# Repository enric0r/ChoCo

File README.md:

# ChoCo

**A USB MIDI chord controller built around a Raspberry Pi Pico.**

Choose a scale, hold a degree key, and move the joystick to change the chord. ChoCo sends MIDI notes to a software instrument, DAW, or compatible MIDI host; the connected instrument produces the sound. The OLED shows the current chord and playing modes.

[Website](https://enric0r.github.io/choco.github.io/) · [English handbook](https://enric0r.github.io/choco.github.io/docs/) · [Guida in italiano](https://enric0r.github.io/choco.github.io/it/docs/) · [Releases](https://github.com/enric0r/ChoCo/releases)

## What you can play

- **Chords in a scale.** Seven degree keys select diatonic chords. Change the root note and choose from nine scales.
- **Chord variations.** Move the joystick for suspensions, sevenths, extensions and other variations. Return it to the center for the base triad.
- **Different ways to play.** Use latch to sustain a chord, add a bass note, stagger notes with strum, or switch to single notes.
- **Inversions and voicing.** Store an inversion for each degree or enable smart voicing.
- **Feedback on the device.** The 128×64 OLED shows key, scale, chord, mode badges and harmonic suggestions.

ChoCo sends class-compliant USB MIDI through TinyUSB. This repository contains the firmware, KiCad hardware files and [STL files for the case](hardware/case/).

## Play your first chord

For an assembled controller:

1. Install the firmware if needed. Download a UF2 from [Releases](https://github.com/enric0r/ChoCo/releases), when available, or [build it below](#build-and-flash).
2. Connect ChoCo with a USB **data** cable.
3. Select its USB MIDI input in your DAW or MIDI host and load an instrument.
4. Hold key `0` to play the first degree of the selected scale.
5. Move the joystick while holding the key, then return it to the center to hear the base chord again.

Start with the [English setup guide](https://enric0r.github.io/choco.github.io/docs/#get-started) or [guida italiana](https://enric0r.github.io/choco.github.io/it/docs/#get-started) for the full walkthrough.

## Controls at a glance

The two upper rows sit halfway between the four white keys. Labels below follow the firmware:

```text
  A   B   C
  1   3   5
0   2   4   6
```

| Control | Action |
| --- | --- |
| `0–6` | Play one of the seven scale degrees |
| `A` | Raise the root by one semitone |
| `B` | Select the next scale |
| `C` | Hold as a modifier for shortcuts |
| Joystick tilt, with a degree held | Change the chord variation |
| `C` + `0–6` | Cycle the inversion for that degree |
| `C` + `A` | Toggle chord latch when A is released; cancelled if the joystick button is used for strum |
| Joystick short press, without `C` | Stop the chord and cancel pending strum notes, keeping the selected modes |
| Joystick long press, without `C` | Toggle single-note mode |

The [illustrated control map](https://enric0r.github.io/choco.github.io/docs/#controls) covers bass, strum, octave changes and the other shortcuts. See [chord variations](https://enric0r.github.io/choco.github.io/docs/#shape-a-chord) for the three joystick maps and [modes and display](https://enric0r.github.io/choco.github.io/docs/#modes-and-display) for the OLED guide.

## Build and flash

Install PlatformIO, then open this repository in a terminal or in VS Code with the PlatformIO extension. The firmware uses the Arduino RP2040 core and the `pico` environment.

```powershell
pio run
```

The UF2 file is written to `.pio/build/pico/firmware.uf2`. To install it:

1. Disconnect the Pico.
2. Hold **BOOTSEL** while connecting it over USB.
3. Copy the UF2 to the **RPI-RP2** drive. The board restarts automatically.

You can also upload through PlatformIO:

```powershell
pio run -t upload
```

`platformio.ini` sets `upload_port = COM5` for local development. Override it locally if your board uses another port. Keep the TinyUSB and network-disable build flags: they are required for this USB MIDI setup.

Serial logging is disabled by default. For diagnostics, set `CHOCO_LOG_LEVEL` in [Config.h](lib/Config/Config.h), rebuild, and run `pio device monitor`. See [DEBUGGING.md](DEBUGGING.md) for the diagnostic steps.

## Hardware and configuration

The prototype uses a Raspberry Pi Pico, ten keys wired as a 3×4 matrix, an analog joystick with a push switch, and an SSD1306-compatible 128×64 I²C OLED.

| Connection | Default pins |
| --- | --- |
| Keypad rows | GP2, GP1, GP0 |
| Keypad columns | GP3, GP4, GP5, GP6 |
| Joystick X / Y | A0 / A1 |
| Joystick switch | GP13 |
| OLED SDA / SCL | GP14 / GP15, on `Wire1` |

The [hardware directory](hardware/) contains the [schematic](hardware/ChoCo.kicad_sch), [PCB layout](hardware/ChoCo.kicad_pcb), [KiCad project](hardware/ChoCo.kicad_pro) and [REV-02 archive](hardware/ChoCo_REV-02.zip).

### 3D-printed case

The [case files and printing notes](hardware/case/) include three separate STL models exported from the Fusion 360 design:

- [Top frame](hardware/case/ChoCo-top.stl)
- [Chocolate-bar bottom](hardware/case/ChoCo-bar-bottom.stl)
- [Joystick cap](hardware/case/ChoCo-thumbstick.stl)

Import the files in millimeters at 100% scale. Each file contains one part; no slicer profile is included yet.

### Prototype bill of materials

For one ChoCo, the project files describe the parts below. This is a record of
the prototype design; exact purchased models and suppliers are still being
confirmed. See the [detailed BOM and assembly notes](hardware/BOM.md).

| Qty | Part | Project detail |
| --- | --- | --- |
| 1 | ChoCo PCB | Prototype marked REV-02 |
| 1 | Raspberry Pi Pico | RP2040 module, `A1` |
| 1 | 128×64 I²C OLED | SSD1306-compatible firmware; `J1` |
| 1 | Two-axis analog joystick with push switch | PS4-style footprint; exact model to confirm |
| 10 | Mechanical key switches | MX-style 1u PCB footprints; `S1–S10` |
| 10 | Matrix diodes | Axial DO-35 footprints; `D1–D10`; symbol describes the 1N4148 family |
| 10 | Keycaps | Visible in the prototype; exact model to confirm |
| 1 | Enclosure / base assembly | Visible in the prototype; fabrication details to confirm |
| 1 | USB data cable | Match the connector on the installed Pico |

Headers, sockets and mounting hardware depend on the actual assembly; they are
listed separately in the detailed BOM so they are not mistaken for additional
schematic components.

Pin assignments, joystick orientation and thresholds, display timings, logging and mode defaults live in [lib/Config/Config.h](lib/Config/Config.h). The [hardware guide](https://enric0r.github.io/choco.github.io/docs/#hardware) and [configuration reference](https://enric0r.github.io/choco.github.io/docs/#configuration) explain these settings.

## Developing the firmware

| Path | Purpose |
| --- | --- |
| [src/main.cpp](src/main.cpp) | Setup and main loop |
| [lib/Controls](lib/Controls/) | Keypad and joystick input |
| [lib/ChordEngine](lib/ChordEngine/) | Chords, inversions, voicing and history |
| [lib/Display](lib/Display/) | OLED rendering and status |
| [lib/MIDI](lib/MIDI/) | USB MIDI transport |
| [lib/Config](lib/Config/) | Shared configuration |
| [test/logic](test/logic/) | Host-side logic tests |

Read [CONTRIBUTING.md](CONTRIBUTING.md) before changing the firmware. Keep the main loop responsive and put hardware settings in `Config.h`.

<details>
<summary>OLED and input implementation notes</summary>

### OLED layout

The header shows the selected key/scale and active degree (`D1..D7`), or `EDIT`
while C is held. The chord is centered at the largest size that fits. The arrow
tracks joystick direction with the horizontal mirror removed; the existing
vertical mapping is preserved for the mounted device.

Active modes appear as a compact text line: `VOI` (smart voicing), `BAS` (bass),
`NOTE` (single note), `STR` (strum), `LAT` (latch). The footer normally shows
`NEXT` suggestions. Temporary confirmations replace only the footer so the
chord stays readable. Long text is fitted or explicitly truncated.

Startup uses a static CHOCO wordmark. The screensaver moves the same wordmark
with the selected key/scale on a separate line; it does not blink or invert.

### Responsiveness and feedback

- Each key and the joystick button use a 10 ms stable-edge debounce, including releases. A newly pressed degree takes over from a held degree; releasing it stops playback unless latch is enabled. Previously held degrees do not retrigger automatically. Exactly simultaneous presses select the lowest degree.
- Strum note-ons are scheduled without blocking input, and pending notes are cancelled on release or chord replacement. Smart voicing preserves only notes that have actually started.
- OLED updates remain limited to 100 ms, skip unchanged frames, and wait for pending strum notes. The first key press wakes the screen and performs its action. Sounding chords keep the screen awake.
- Joystick feedback and new chord attacks share the same hysteresis state, so a variation remains selected until the stick crosses the release threshold. Degree release is processed before joystick changes to prevent a brief extra chord on release.
- Chord names use the lowest note of the resulting voicing for slash notation, including the optional bass pedal. Bass toggles apply immediately; other voicing settings apply when the next chord is generated. The top bar shows the selected key/scale, while the main name describes the active chord.
- Display degrees `1..7` correspond to physical keys `0..6`. `NEXT` contains harmonic suggestions, not a prediction or a correctness score.
- Chord names, history and status messages use fixed buffers. Release builds keep serial output disabled; `C+B` reports this on screen unless INFO logging is enabled.

These are software guarantees covered where possible by host tests. End-to-end latency, matrix ghosting with multiple keys, OLED appearance and USB behaviour still require testing on the physical board and MIDI host.

</details>

### Testing

CI runs six host test programs and builds the firmware with `pio run`. Host tests need a native C++17 compiler; `pio test` is not configured.

<details>
<summary>Run the host logic tests with PowerShell</summary>

```powershell
New-Item -ItemType Directory -Force .test | Out-Null

g++ -std=c++17 -Wall -Wextra -pedantic -Ilib/ChordEngine test/logic/test_chord_logic.cpp -o .test/choco_logic_tests.exe
.test/choco_logic_tests.exe

g++ -std=c++17 -Wall -Wextra -pedantic -Ilib/Controls test/logic/test_joystick_direction.cpp -o .test/choco_joystick_tests.exe
.test/choco_joystick_tests.exe
```

</details>

USB delivery, joystick behavior and the OLED also need checks on a real controller and MIDI host. Follow the hardware checks in [DEBUGGING.md](DEBUGGING.md).

Run the complete suite on Linux, macOS or WSL with a native C++ compiler:

```bash
bash test/run_host_tests.sh
```

On Windows with Ubuntu installed in WSL: `wsl -d Ubuntu -- bash test/run_host_tests.sh`.
The suite covers degree bounds, scale wrapping, inversions, joystick classification, contact bounce, timer rollover, cancellable strum, overlapping keys, latch/strum shortcuts, bass ownership and chord labels. The integration test runs the actual main loop, controls and chord engine with simulated GPIO, time and MIDI. It does not emulate USB or OLED hardware. A cross-compiler such as `arm-none-eabi-g++` cannot run these host tests.

## Help and documentation

For missing MIDI input, a blank OLED or unexpected controls, start with the [troubleshooting guide](https://enric0r.github.io/choco.github.io/docs/#troubleshooting). For a reproducible problem, [open an issue](https://github.com/enric0r/ChoCo/issues).

The handbook is available in [English](https://enric0r.github.io/choco.github.io/docs/) and [Italian](https://enric0r.github.io/choco.github.io/it/docs/), with control diagrams and OLED examples. Its source lives in [choco.github.io](https://github.com/enric0r/choco.github.io).

## License

ChoCo is distributed under the [PolyForm Noncommercial License 1.0.0](LICENSE).

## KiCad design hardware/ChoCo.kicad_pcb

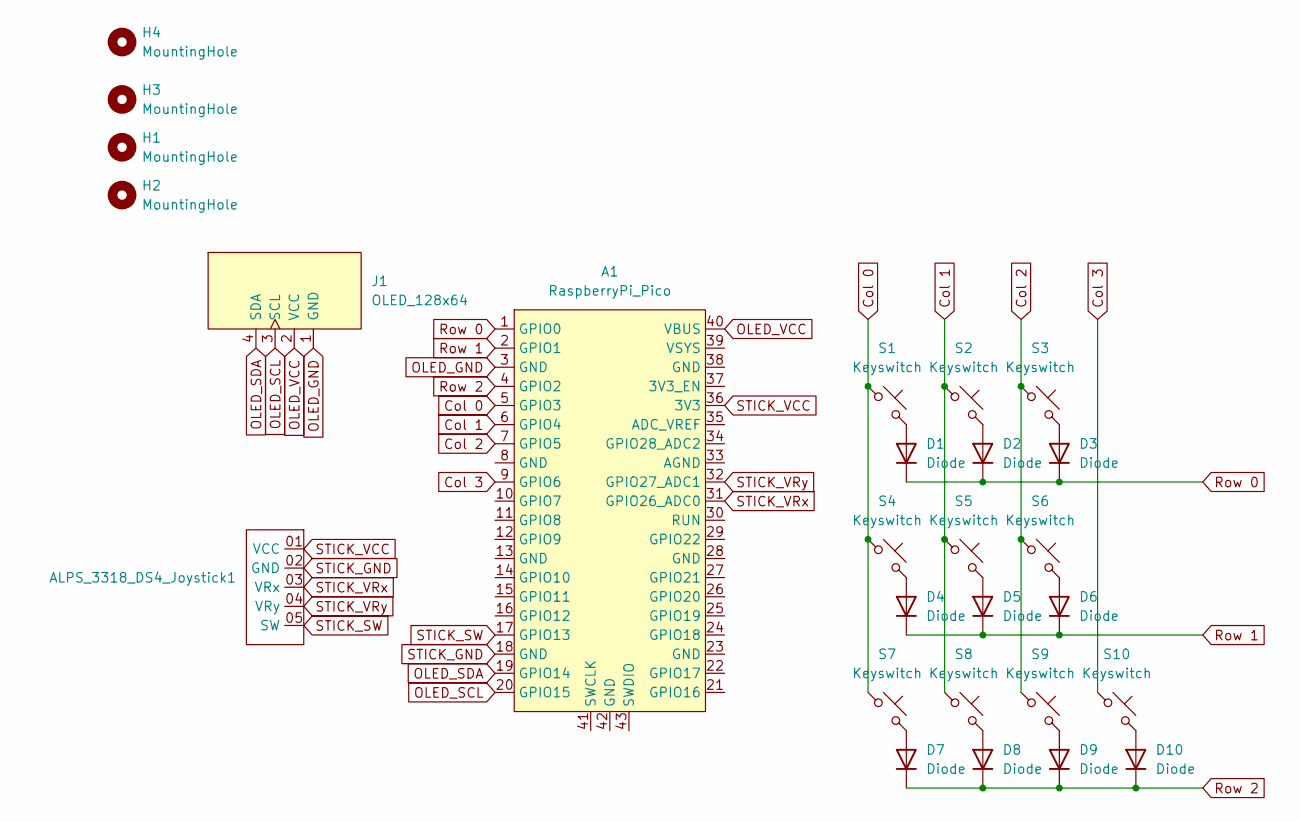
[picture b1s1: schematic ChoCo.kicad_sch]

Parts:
A1: RaspberryPi_Pico; Raspberry_Pi_Pico
ALPS_3318_DS4_Joystick1: PS4_joystick
D1, D2, D3, D4, D5, D6, D7, D8, D9, D10: Diode; Diode_DO-35
H1, H2, H3, H4: MountingHole; MountingHole_2.2mm_M2
J1: OLED_128x64
S1, S2, S3, S4, S5, S6, S7, S8, S9, S10: Keyswitch; MX_PCB_1.00u

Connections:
Col 0: A1.5 (GPIO3), S1.1, S4.1, S7.1
Col 1: A1.6 (GPIO4), S2.1, S5.1, S8.1
Col 2: A1.7 (GPIO5), S3.1, S6.1, S9.1
Col 3: A1.9 (GPIO6), S10.1
unnamed: D1.2 (A), S1.2
unnamed: D2.2 (A), S2.2
unnamed: D3.2 (A), S3.2
unnamed: D4.2 (A), S4.2
unnamed: D5.2 (A), S5.2
unnamed: D6.2 (A), S6.2
unnamed: D7.2 (A), S7.2
unnamed: D8.2 (A), S8.2
unnamed: D9.2 (A), S9.2
unnamed: D10.2 (A), S10.2
OLED_GND: A1.3 (GND), J1.1 (GND)
OLED_SCL: A1.20 (GPIO15), J1.3 (SCL)
OLED_SDA: A1.19 (GPIO14), J1.4 (SDA)
OLED_VCC: A1.40 (VBUS), J1.2 (VCC)
Row 0: A1.1 (GPIO0), D1.1 (K), D2.1 (K), D3.1 (K)
Row 1: A1.2 (GPIO1), D4.1 (K), D5.1 (K), D6.1 (K)
Row 2: A1.4 (GPIO2), D7.1 (K), D8.1 (K), D9.1 (K), D10.1 (K)
STICK_GND: A1.18 (GND), ALPS_3318_DS4_Joystick1.02 (GND)
STICK_SW: A1.17 (GPIO13), ALPS_3318_DS4_Joystick1.05 (SW)
STICK_VCC: A1.36 (3V3), ALPS_3318_DS4_Joystick1.01 (VCC)
STICK_VRx: A1.31 (GPIO26_ADC0), ALPS_3318_DS4_Joystick1.03 (VRx)
STICK_VRy: A1.32 (GPIO27_ADC1), ALPS_3318_DS4_Joystick1.04 (VRy)

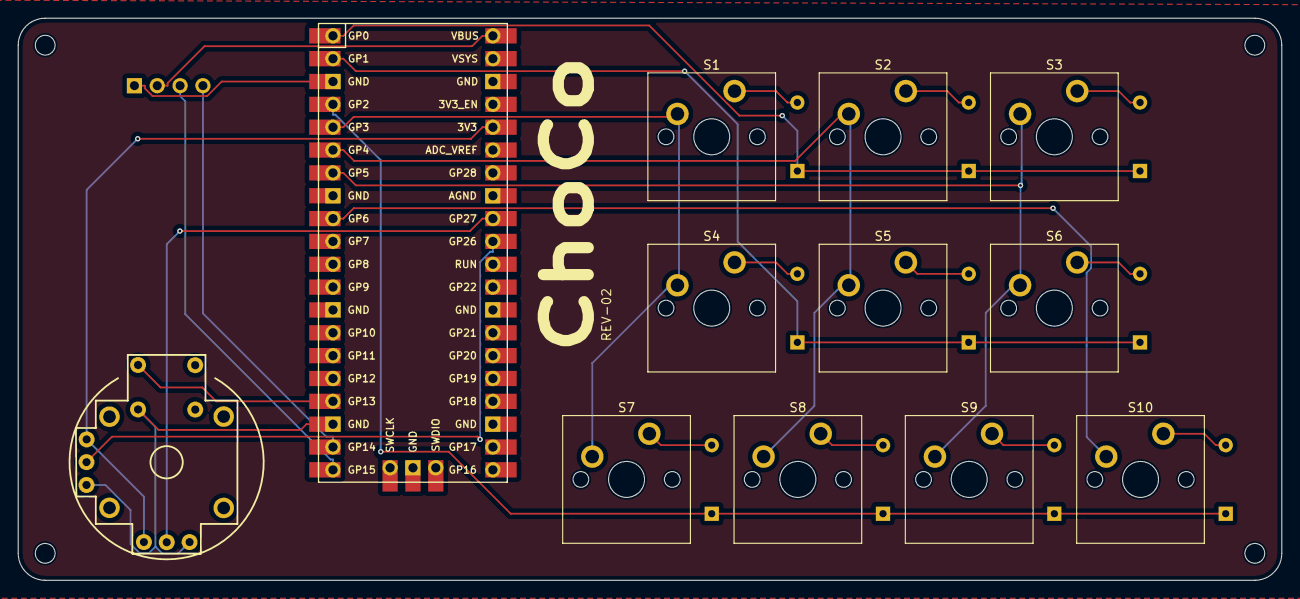
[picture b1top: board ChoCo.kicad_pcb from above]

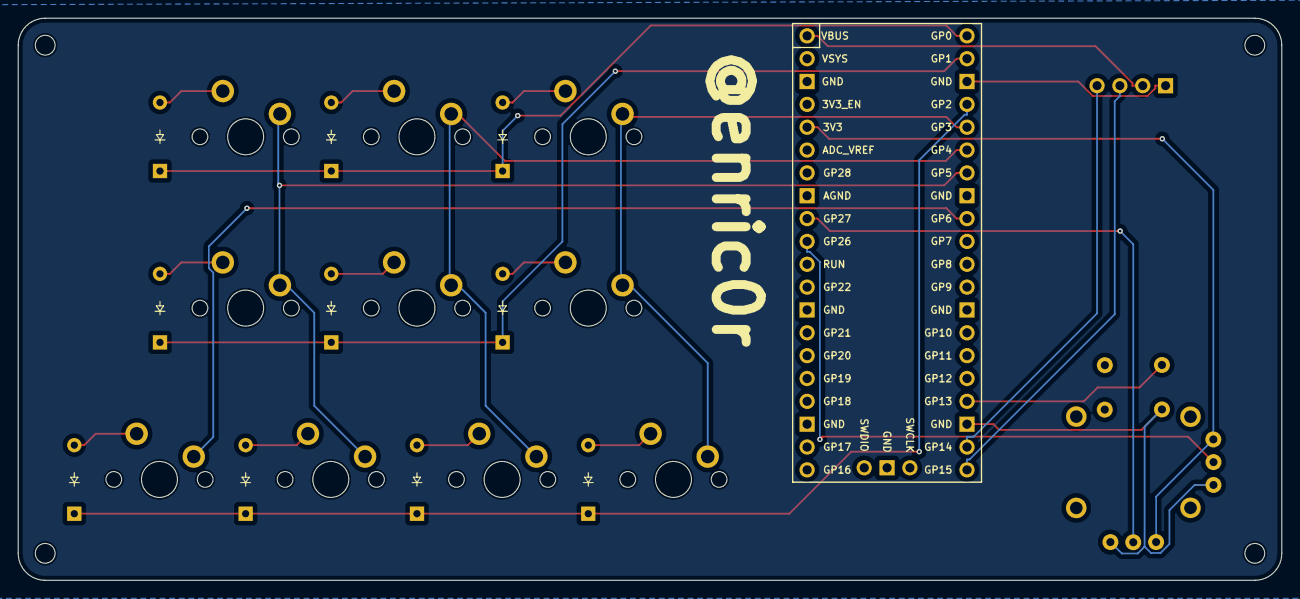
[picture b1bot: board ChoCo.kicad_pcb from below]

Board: 2 copper layers, 140.5 x 62.5 mm, 26 parts (10 on the bottom side), 21 nets.

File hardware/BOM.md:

# ChoCo prototype BOM

This records the hardware described by the repository and visible in the prototype
photos, for **one controller**. It is the starting point for documenting the
builder's actual parts. Exact purchase links, manufacturers and variants remain
to be confirmed; a library label is not proof of the part purchased.

## Electronic parts

| Qty | Part | Reference | Evidence / assembly detail |
| --- | --- | --- | --- |
| 1 | Raspberry Pi Pico, RP2040 | A1 | Schematic value `RaspberryPi_Pico`; PCB footprint `ScottoKeebs_MCU:Raspberry_Pi_Pico`; module visible in the front photo. The symbol description also mentions Pico 2, but this does not establish firmware support for Pico 2. |
| 1 | 128×64 I²C OLED module | J1 | Schematic value `OLED_128x64`; footprint `ScottoKeebs_Components:OLED_128x64`. Firmware targets SSD1306 at `0x3C`. The connector reference represents the display module, not a second display. Exact module size and supplier are not recorded. |
| 1 | Two-axis analog joystick with push switch | ALPS_3318_DS4_Joystick1 (schematic) | Footprint `PS4_Joystick:PS4_joystick`. The PCB uses `REF**` and value `XDCR_COM-09032`; these inconsistent labels are not treated as a confirmed manufacturer part number. Confirm the installed joystick before using a purchase link. |
| 10 | Mechanical key switches | S1–S10 | `Scotto_MX:MX_PCB_1.00u` footprints. Switch brand, variant and operating force are not recorded. |
| 10 | Matrix diodes, axial DO-35 | D1–D10 | Value `Diode`, footprint `Scotto:Diode_DO-35`. The symbol description mentions 1N4148 / 1N4148W, but the PCB footprint is axial DO-35, not the SOD-123 package also mentioned by that generic description. Exact installed diode part number is unconfirmed. |

The schematic contains **23 physical electronic items in five groups**. It has no
populated manufacturer/MPN fields. Counts and footprints above were extracted
from the schematic and compared with the PCB; this is an inventory consistency
check, not an electrical or manufacturer-datasheet validation.

## Board and assembly items

| Qty | Item | Evidence / what remains to record |
| --- | --- | --- |
| 1 | ChoCo PCB | Front photo shows REV-02; source PCB and a REV-02 archive are included. Check the actual revision before fabrication. |
| 10 | Keycaps | Front photo shows 3 dark, 3 brown and 4 light caps. Material, dimensions and purchase or fabrication source are unconfirmed. |
| 1 assembly | Enclosure / base | Visible in front/back photos. Material, fabrication files and method are not established by these KiCad files. |
| 4 visible positions | Mounting hardware | PCB has H1–H4, `MountingHole_2.2mm_M2`; fasteners are visible in the photos. Actual screw length, nuts and spacers need confirmation. Hole footprints are not four extra electronic components. |
| As fitted | Headers / sockets | Pico and OLED connection method and separate header quantities need confirmation; do not double-count headers already supplied with a module. |
| 1 | USB data cable | Required for power and USB MIDI; choose the connector matching the installed module. |

## Details to add from the actual build

- Purchase links or manufacturer/model for the Pico, OLED, joystick and switches.
- Installed diode model and manufacturer, if known.
- Keycap and enclosure source: purchased parts or fabrication files/materials.
- Headers, sockets, screw lengths and spacers actually fitted.

Prices, stock and alternative parts are intentionally omitted: this page records
the prototype rather than selecting replacement parts or preparing an order.

## Sources

- [KiCad schematic](ChoCo.kicad_sch): quantities, values and intended footprints.
- [KiCad PCB](ChoCo.kicad_pcb): placed footprints and four mounting holes.
- [Front photo](front.jpg) and [back photo](back.jpg): visible assembly and REV-02 marking.
- [Firmware configuration](../lib/Config/Config.h): display and input configuration.
- [Project README](../README.md#prototype-bill-of-materials): short BOM.

When a purchased part is confirmed, update this page and the English/Italian
handbook together. Add confirmed manufacturer/MPN properties to the schematic
when maintaining the electrical BOM; do not infer them from a footprint name.

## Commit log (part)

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2024-07-06 Update README.md with basic description and BOM
2024-10-02 Create code.py version zero
2025-05-29 Adding gitignore, fonts and libs
2025-05-30 Added inversions configuration, new chords
2025-05-30 Refactored code in multiple files
2025-05-30 Added missing joystick logic
2025-11-04 Refactor chord handling and display updates; add root tracking for chords, improve status message display, and remove unused I2C test code.
2025-11-04 Add bass mode functionality; implement bass note tracking, toggle controls, and display indicator
2025-11-04 Implement chord inversion and auto-voicing features; add functions for managing inversions, enhance display indicators, and update control handling for improved user interaction.
2025-11-04 Add scale type management; implement scale cycling and update display to show current scale name
2025-11-04 Add chord history functionality; implement storage and display of recent chords, and integrate history printing with user controls.
2025-11-04 Add custom chord playback with joystick variations; implement playChordForDegreeWithIntervals function and joystick direction priming to enhance chord selection.
2025-11-04 Initial plan
2025-11-04 Implement octave change with C modifier + joystick left/right
2025-11-04 Fix duplicate static variable declaration in Controls.cpp
2025-11-04 Improve octave change logic and update documentation
2025-11-04 Address code review feedback - improve octave tracking logic
2025-11-04 Add _codeql_detected_source_root to .gitignore
2025-11-05 Add Clock, Arpeggiator modules and panic function
2025-11-05 Add display updates and documentation for new features
2025-11-05 Fix code review issues - use constants from Config.h
2025-11-05 Fix logic errors in clock and inversion editing
2025-11-05 Add timing/clock system, arpeggiator, and panic function
2025-11-05 Add roadmap for future features including performance enhancements, harmony voicing, scale management, and user controls
2025-11-05 Remove CodeQL artifact and update .gitignore
2025-11-06 Fix type casting in midiPanic function for MIDI All Notes Off command
2025-11-06 Enhance chord display and debugging information
    - Added debug logging in getCurrentChordName() to indicate when no active chord is present.
    - Improved updateDisplay() to always show chord information, with status messages overlaid.
    - Added handling for displaying "---" when no chord is active.
    - Refactored display logic to ensure chord name and status are displayed correctly.
    - Added debug output for chord drawing and display completion.
2025-11-07 Refactor chord playback and display logic
    - Updated `playChord` function in `ChordEngine.cpp` to improve chord name formatting, including slash notation for inversions.
    - Enhanced logging to include detailed chord information with inversion and bass note.
    - Modified joystick handling in `Controls.cpp` to streamline button press detection, including long press functionality for toggling auto-voicing.
    - Improved display updates in `Display.cpp` to show abbreviated scale names and centered chord history.
    - Added `getScaleAbbreviation` function in `Display.h` and `Display.cpp` for compact display of scale names.
2025-11-07 Remove space replacement from chord display logic
2025-11-07 Add "E" badge for Edit mode in display update logic
2025-11-07 Add Controls, Display, and MIDI modules for ChoCo project
    - Implement Controls module with key and joystick handling functions.
    - Create Display module for OLED display management, including splash screen and status updates.
    - Develop MIDI module for USB MIDI communication, including note on/off functions and a test sequence.
    - Update library.json files for each module to define dependencies and metadata.
2025-11-07 Invert joystick X-axis reading to accommodate upside-down mounting
2025-11-07 Add GitHub Actions workflow for building ChoCo MIDI Controller firmware
2025-11-07 Add release creation step to GitHub Actions workflow with detailed release notes; Removed build on push and pull_request
2025-11-07 Add permissions section to GitHub Actions workflow for content write access
2025-11-07 Update GitHub Actions release action to version 2 for improved functionality
2025-11-08 Add screensaver functionality with timeout and animation support
2025-11-08 Refactor screensaver animation interval for smoother transitions and simplify logo display logic
2025-11-15 Enhance joystick handling to toggle modes based on 'C' modifier state during button press
2026-02-24 feat: Enhance control handling with joystick support and chord variations
    - Introduced JoystickDirection enum for better joystick direction classification.
    - Added ControlSnapshot struct to encapsulate control states including joystick and key states.
    - Implemented pollControls function to read and update control states in a single call.
    - Updated handleJoystick function to accept additional parameters for modifier key and joystick button state.
    - Added chord variation retrieval based on joystick direction.
    - Refactored main loop to utilize new control polling and joystick handling logic.
2026-03-15 Refactor controls and display handling; add contributing guidelines and license
    - Updated Controls.h to modify function signatures for chord variations and joystick handling.
    - Enhanced Display.cpp with new badges for single note, strum, and latch modes; optimized string handling for history display.
    - Changed Display.h to reflect updated function signatures.
    - Modified main.cpp to accommodate new joystick handling and chord latch functionality.
    - Added CONTRIBUTING.md to outline contribution process and guidelines.
    - Introduced LICENSE file with PolyForm Noncommercial License 1.0.0 for project usage.
2026-03-15 Added pcb files
2026-04-07 Add images to README.md
